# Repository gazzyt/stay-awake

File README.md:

A simple firmware for keeping PCs awake. In a corporate environment we often have to put up with a managed desktop which is set to lock after a short period of inactivity and we are not able to change that configuration. Well you could build a robot to wiggle your mouse every so often or you could build one of these devices which presents itself to the host as a USB mouse and every minute it moves that mouse 1 pixel left and then right again. You'd have to look very carefully to notice yourself but it's enough to keep the PC thinking you are active!

Hardware
========
Design files are shown in the hardware folder and were drawn with KiCad version (5.1.9)-1. The printable folder contains the following:
* a schematic PDF
* a pcb design PDF
* a PDF plot in mirrored negative which I used to create the PCB with negative photo-resist film

Firmware
========
The firmware is built on the fantastic [v-usb](https://github.com/obdev/v-usb) USB driver which provides USB capabilities to AVR devices that lack USB hardware. I have modified one of their samples.

The firmware is built with Microchip Studio 7.0.2542.

Programming
-----------
Set fuses as shown

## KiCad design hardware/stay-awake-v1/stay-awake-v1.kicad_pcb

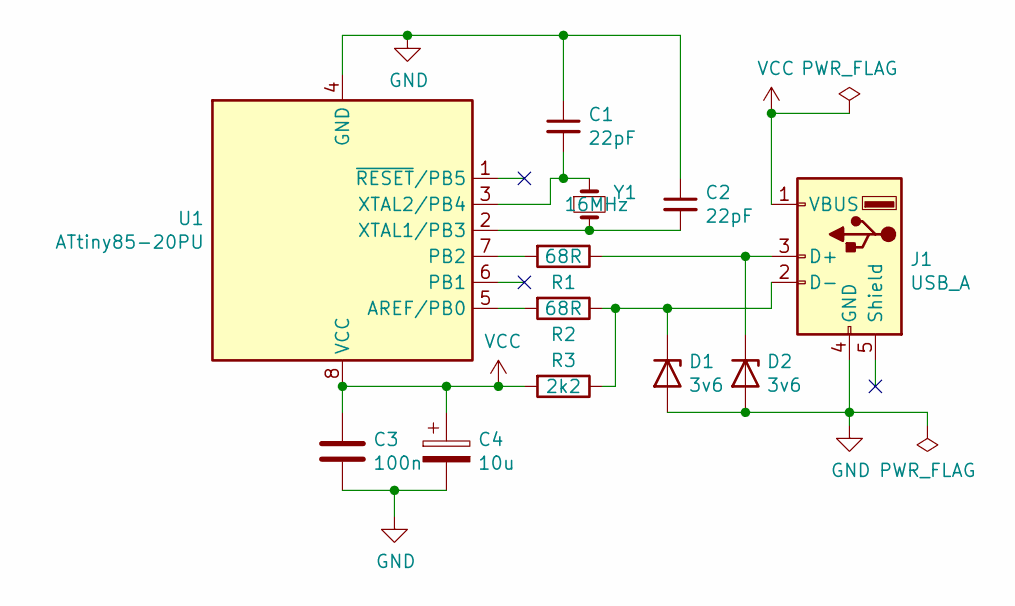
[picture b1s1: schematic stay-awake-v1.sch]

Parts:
C1, C2: 22pF; C_Disc_D3.0mm_W1.6mm_P2.50mm
C3: 100n; C_Disc_D5.0mm_W2.5mm_P5.00mm
C4: 10u; CP_Radial_Tantal_D5.0mm_P2.50mm
D1, D2: 3v6; D_A-405_P7.62mm_Horizontal
J1: USB_A
R1, R2: 68R; R_Axial_DIN0207_L6.3mm_D2.5mm_P7.62mm_Horizontal
R3: 2k2; R_Axial_DIN0207_L6.3mm_D2.5mm_P7.62mm_Horizontal
U1: ATtiny85-20PU; DIP-8_W7.62mm
Y1: 16MHz; Resonator-2pin_w8.0mm_h3.5mm

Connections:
GND: C1.1, C2.1, C3.2, C4.2, D1.2 (A), D2.2 (A), J1.4 (GND), U1.4 (GND)
unnamed: C1.2, U1.3 (XTAL2/PB4), Y1.1
unnamed: C2.2, U1.2 (XTAL1/PB3), Y1.2
unnamed: D1.1 (K), J1.2 (D-), R2.1, R3.1
unnamed: D2.1 (K), J1.3 (D+), R1.1
unnamed: R1.2, U1.7 (PB2)
unnamed: R2.2, U1.5 (AREF/PB0)
VCC: C3.1, C4.1, J1.1 (VBUS), R3.2, U1.8 (VCC)

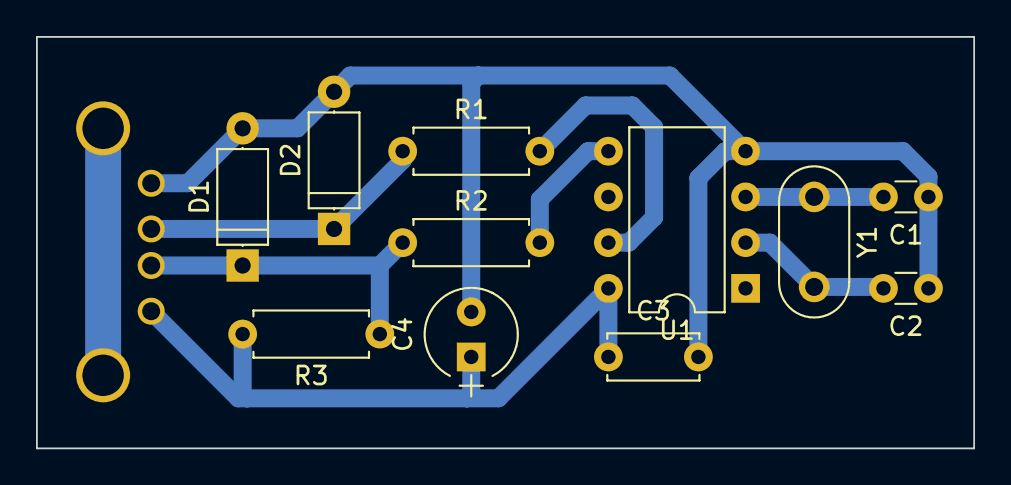
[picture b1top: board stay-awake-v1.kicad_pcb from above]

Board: 2 copper layers, 52.1 x 22.9 mm, 12 parts (1 on the bottom side), 8 nets.

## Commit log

2021-04-01 Initial project - sample copied from SDK
2021-04-01 Add schematic
2021-04-05 Add pcb
2021-04-15 jiggle the mouse every minute
2021-04-15 Add readme
